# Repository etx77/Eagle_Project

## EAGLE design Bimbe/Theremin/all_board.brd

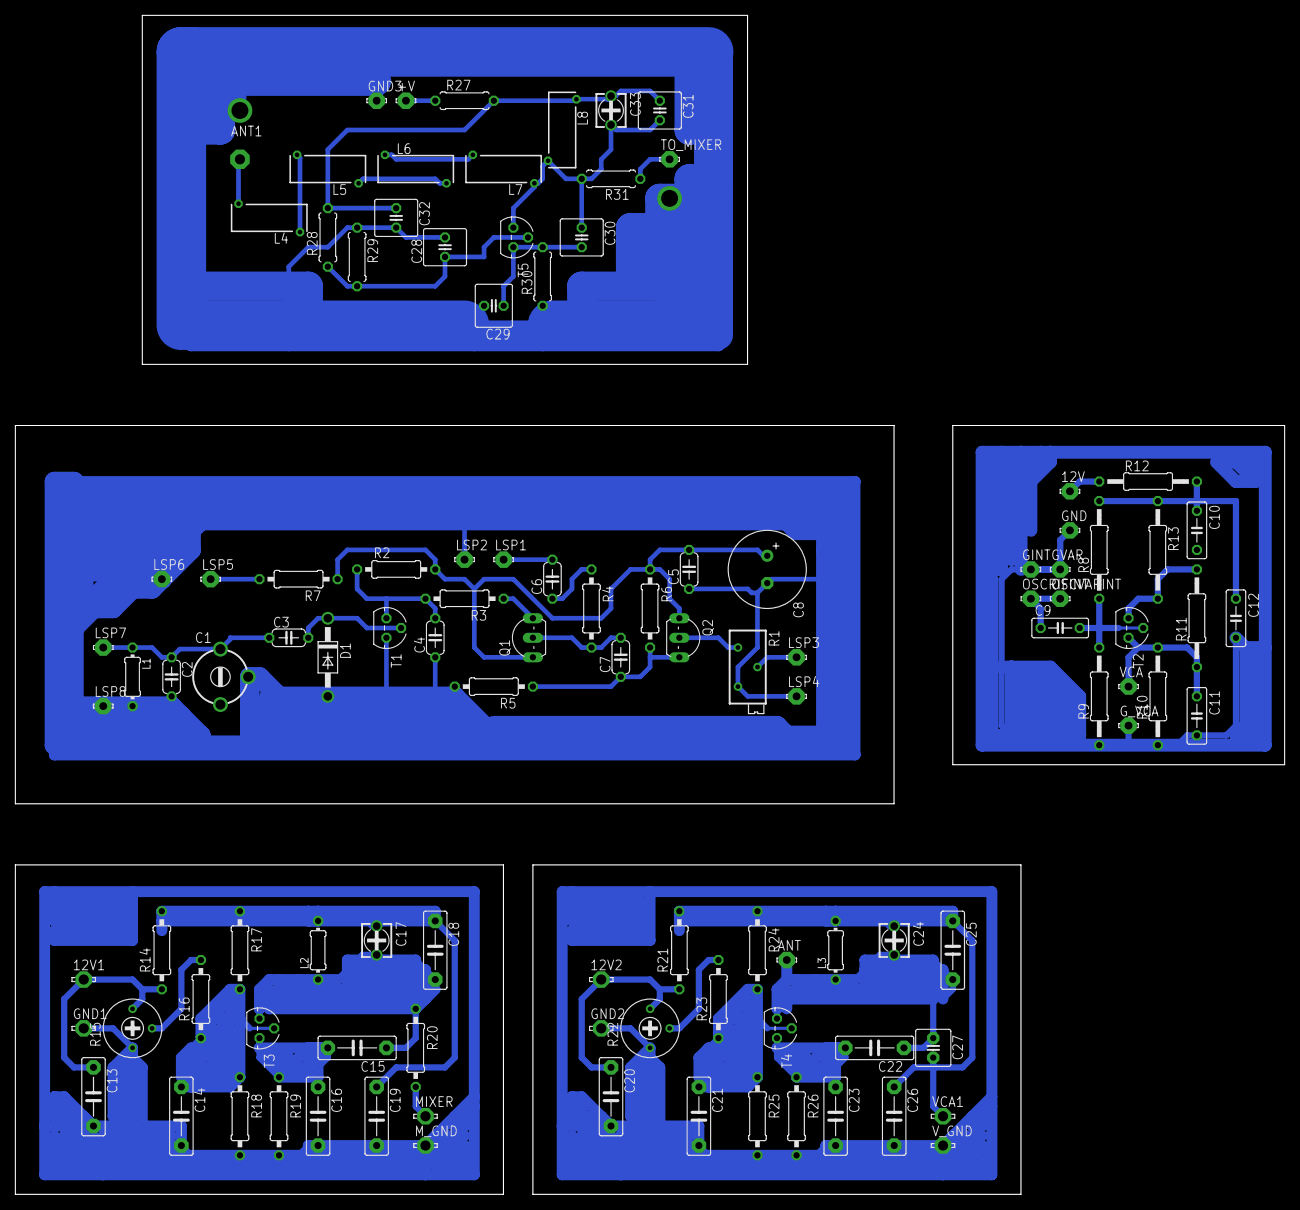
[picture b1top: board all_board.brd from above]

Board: 2 copper layers, 165.1 x 153.3 mm, 109 parts (0 on the bottom side), 47 nets.

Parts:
12V: LSP10
12V1, 12V2: LSP13
+V: LSP10
ANT: LSP10
ANT1: PAD-01
C1: 10/40pF; CTRIM808-BC
C2: 220pF; C050-024X044
C3, C6: 4,7pF; C050-024X044
C4, C5: 100nF; C050-024X044
C7: 1nF; C050-024X044
C8: 10uF; E3,5-10
C9: 10nF; C050-025X075
C10, C11: 4,7nF; C050-025X075
C12: 100nF; C050-025X075
C13, C14, C20, C21: 100nF; C7.5B3
C15: 680pF; C7.5B3
C16, C19, C26: 33nF; C7.5B3
C17, C24: 10/40 pF; 3008
C18, C25: 220pF; C7.5B3
C22: 270pF; C7.5B3
C23: 12nF; C7.5B3
C27: 4,7pF; C2.5-5
C28: 100nF; C025-060X050
C29, C32: 33nF; C025-060X050
C30: 680pF; C025-060X050
C31: 220pF; C025-060X050
C33: 10/40pF; 3008
D1: 1N4004; DO41-10
GINT: LSP10
GND, GND3: LSP10
GND1, GND2: LSP13
GVAR: LSP10
G_VCA: LSP10
L1, L3: 330uH; 0204/7
L2: 1mH; 0204/7
L4, L5, L6, L7: 10mH; Z28/7
L8: 1mH; Z28/7
LSP1, LSP2, LSP3, LSP4, LSP5, LSP6, LSP7, LSP8: LSP10
MIXER: LSP13
M_GND: LSP13
OSCRIFINT: LSP10
OSCVARINT: LSP10
Q1, Q2: 2N5486; TO92-
R1: 10K log; RTRIMT93XB
R2: 10K; 0207/10
R3: 470K; 0207/10
R4, R23: 1M; 0207/10
R5, R6: 4,7M; 0207/10
R7, R14, R19, R21, R26: 1K; 0207/10
R8: 560K; 0207/12
R9: 100k; 0207/12
R10, R11, R12: 1K; 0207/12
R13: 6K8; 0207/12
R15, R22: 10K Lin; RTRIM3339P
R16, R20: 330K; 0207/10
R17, R24: 150K; 0207/10
R18, R25: 33K; 0207/10
R27, R30: 1K; 0207/7
R28: 150K; 0207/7
R29: 33K; 0207/7
R31: 330K; 0207/7
T1, T2, T3, T4, T5: BC547; TO92
TO_MIXER: LSP10
VCA: LSP10
VCA1: LSP13
V_GND: LSP13

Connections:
unnamed: C1.1, C2.1, C3.1, L1.1, LSP7.MP
unnamed: C6.2, LSP1.MP
unnamed: C3.2, D1.C, T1.2
unnamed: C4.2, R2.1, R3.2, T1.3
unnamed: C5.2, C8.+, Q1.3, Q2.3, R2.2, R6.1, R7.1
unnamed: Q1.1, R3.1
unnamed: C6.1, R4.1
unnamed: C7.2, Q1.2, R4.2
unnamed: C7.1, Q2.1, R5.1, R6.2
unnamed: Q2.2, R1.1
unnamed: LSP3.MP, R1.2
unnamed: LSP5.MP, R7.2
unnamed: C9.2, R8.1, R9.2, T2.2
unnamed: C10.2, R11.2, R13.2, T2.3
unnamed: C11.1, R10.2, R11.1, T2.1, VCA.MP
unnamed: C1.2, C2.2, C4.1, C5.1, C8.-, D1.A, L1.2, LSP2.MP, LSP4.MP, LSP6.MP, LSP8.MP, R1.3, R5.2, T1.1
unnamed: C10.1, C12.1, R8.2, R12.2, R13.1
unnamed: C9.1, OSCRIFINT.MP, OSCVARINT.MP
unnamed: 12V.MP, R12.1
unnamed: C11.2, C12.2, GINT.MP, GND.MP, GVAR.MP, G_VCA.MP, R9.1, R10.1
unnamed: 12V1.MP, C13.1, R14.1, R15.3
unnamed: C17.+, C18.1, C19.1, L2.2, R14.2, R17.1
unnamed: C14.1, R16.1, R17.2, R18.1, T3.2
unnamed: R15.2, R16.2
unnamed: C15.2, C16.1, R19.1, T3.1
unnamed: MIXER.MP, R20.2
unnamed: C13.2, C14.2, C16.2, C19.2, GND1.MP, M_GND.MP, R15.1, R18.2, R19.2
unnamed: C15.1, C17.-, C18.2, L2.1, R20.1, T3.3
unnamed: 12V2.MP, C20.1, R21.1, R22.3
unnamed: C24.+, C25.1, C26.1, L3.2, R21.2, R24.1
unnamed: C21.1, R23.1, R24.2, R25.1, T4.2
unnamed: R22.2, R23.2
unnamed: C22.2, C23.1, R26.1, T4.1
unnamed: C27.2, VCA1.MP
unnamed: C20.2, C21.2, C23.2, C26.2, GND2.MP, R22.1, R25.2, R26.2, V_GND.MP
unnamed: ANT.MP, C22.1, C24.-, C25.2, C27.1, L3.1, T4.3
unnamed: C31.1, C32.1, C33.+, L8.2, R27.2, R28.2
unnamed: ANT1.1, L4.1
unnamed: L4.2, L5.1
unnamed: L5.2, L6.1
unnamed: L6.2, L7.1
unnamed: C30.1, C31.2, C33.-, L7.2, L8.1, R31.2, T5.3
unnamed: C28.1, R28.1, R29.2, T5.2
unnamed: C29.1, C30.2, R30.2, T5.1
unnamed: R31.1, TO_MIXER.MP
unnamed: +V.MP, R27.1
unnamed: C28.2, C29.2, C32.2, GND3.MP, R29.1, R30.1

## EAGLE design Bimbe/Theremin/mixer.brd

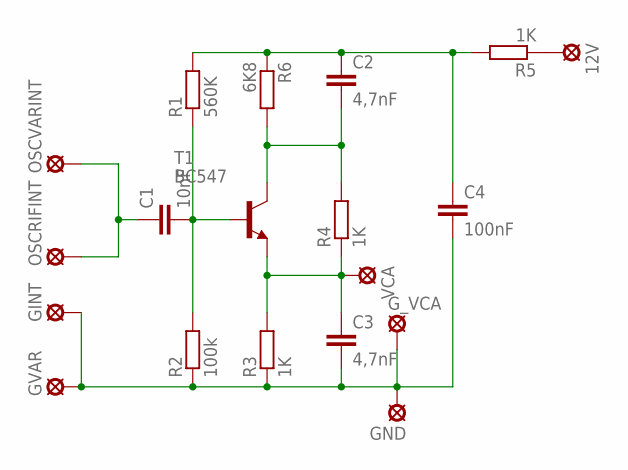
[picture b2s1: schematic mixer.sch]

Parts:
12V: LSP10
C1: 10nF; C050-025X075
C2, C3: 4,7nF; C050-025X075
C4: 100nF; C050-025X075
GINT: LSP10
GND: LSP10
GVAR: LSP10
G_VCA: LSP10
OSCRIFINT: LSP10
OSCVARINT: LSP10
R1: 560K; 0207/12
R2: 100k; 0207/12
R3, R4, R5: 1K; 0207/12
R6: 6K8; 0207/12
T1: BC547; TO92
VCA: LSP10

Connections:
unnamed: C1.2, R1.1, R2.2, T1.2 (B)
unnamed: C2.2, R4.2, R6.2, T1.3 (C)
unnamed: C3.1, R3.2, R4.1, T1.1 (E), VCA.MP
unnamed: C2.1, C4.1, R1.2, R5.2, R6.1
unnamed: C1.1, OSCRIFINT.MP, OSCVARINT.MP
unnamed: 12V.MP, R5.1
unnamed: C3.2, C4.2, GINT.MP, GND.MP, GVAR.MP, G_VCA.MP, R2.1, R3.1

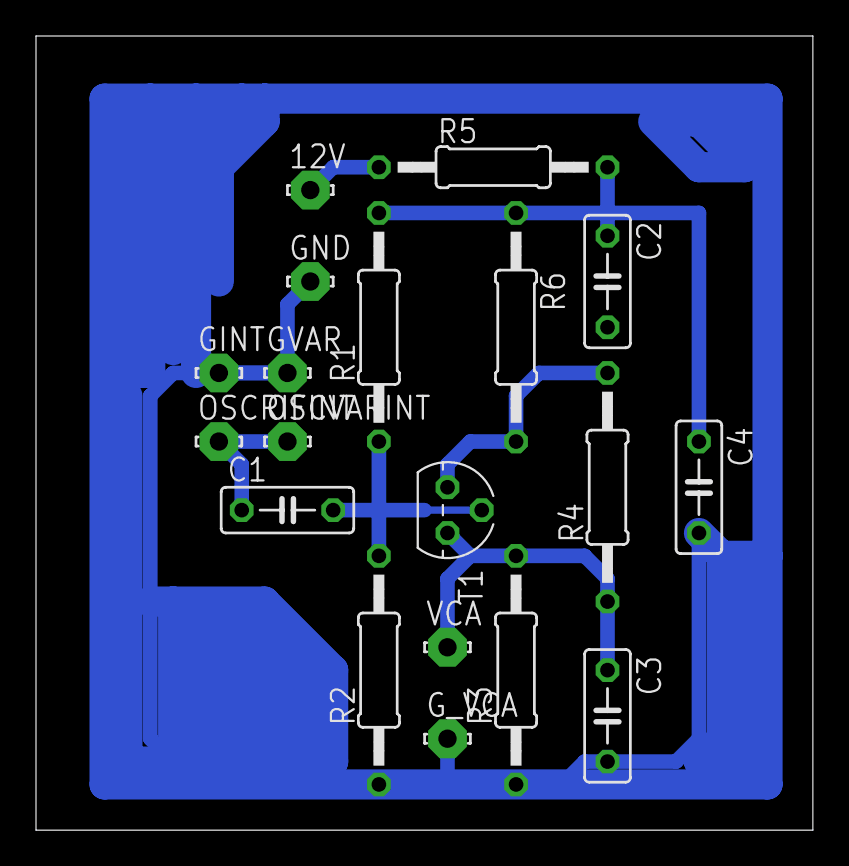
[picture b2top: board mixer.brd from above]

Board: 2 copper layers, 43.2 x 44.1 mm, 19 parts (0 on the bottom side), 7 nets.

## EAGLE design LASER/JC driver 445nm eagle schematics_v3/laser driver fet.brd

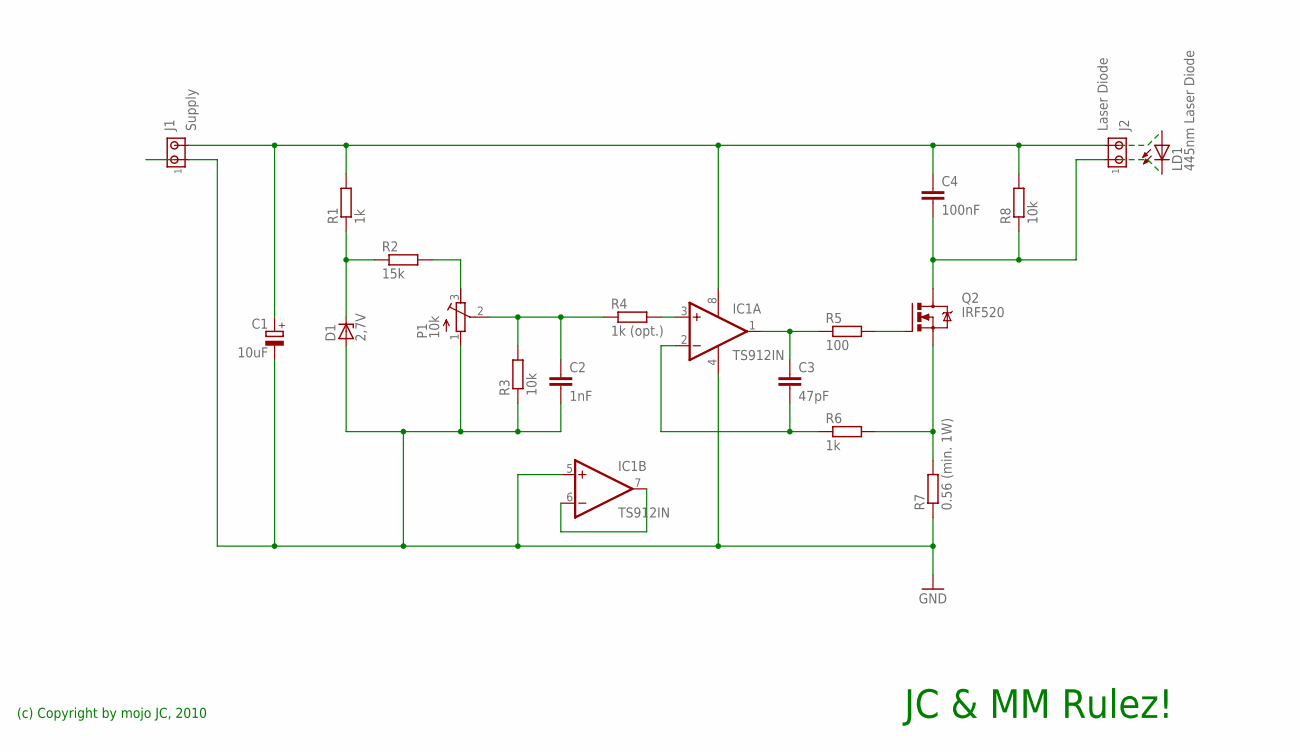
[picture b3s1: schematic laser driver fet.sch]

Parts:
C1: 10uF; E5-13
C2: 1nF; C2.5-3
C3: 47pF; C2.5-3
C4: 100nF; C2.5-3
D1: 2,7V; DO41Z10
IC1: TS912IN; DIL08
J1: Supply; 1X2MTA
J2: Laser Diode; 1X2MTA
LD1: 445nm Laser Diode; LED5MM
P1: 10k; RTRIM3296W
Q2: IRF520; TO220BV
R1, R6: 1k; 0309/10
R2: 15k; 0309/10
R3, R8: 10k; 0309/10
R4: 1k (opt.); 0309/10
R5: 100; 0309/10
R7: 0.56 (min. 1W); 0411V

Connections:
GND: C1.-, C2.2, D1.A, IC1.4 (V-), IC1.5 (+IN), J1.1, P1.1 (E), R3.1, R7.1
unnamed: D1.C, R1.1, R2.1
unnamed: C1.+, C4.1, IC1.8 (V+), J1.2, J2.2, R1.2, R8.2
unnamed: C4.2, J2.1, Q2.D, R8.1
unnamed: P1.3 (A), R2.2
unnamed: IC1.3 (+IN), R4.2
unnamed: C3.2, IC1.2 (-IN), R6.1
unnamed: Q2.S, R6.2, R7.2
unnamed: Q2.G, R5.2
unnamed: C3.1, IC1.1 (OUT), R5.1
unnamed: C2.1, P1.2 (S), R3.2, R4.1
unnamed: IC1.6 (-IN), IC1.7 (OUT)

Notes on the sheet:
(c) Copyright by mojo JC, 2010
JC & MM Rulez!

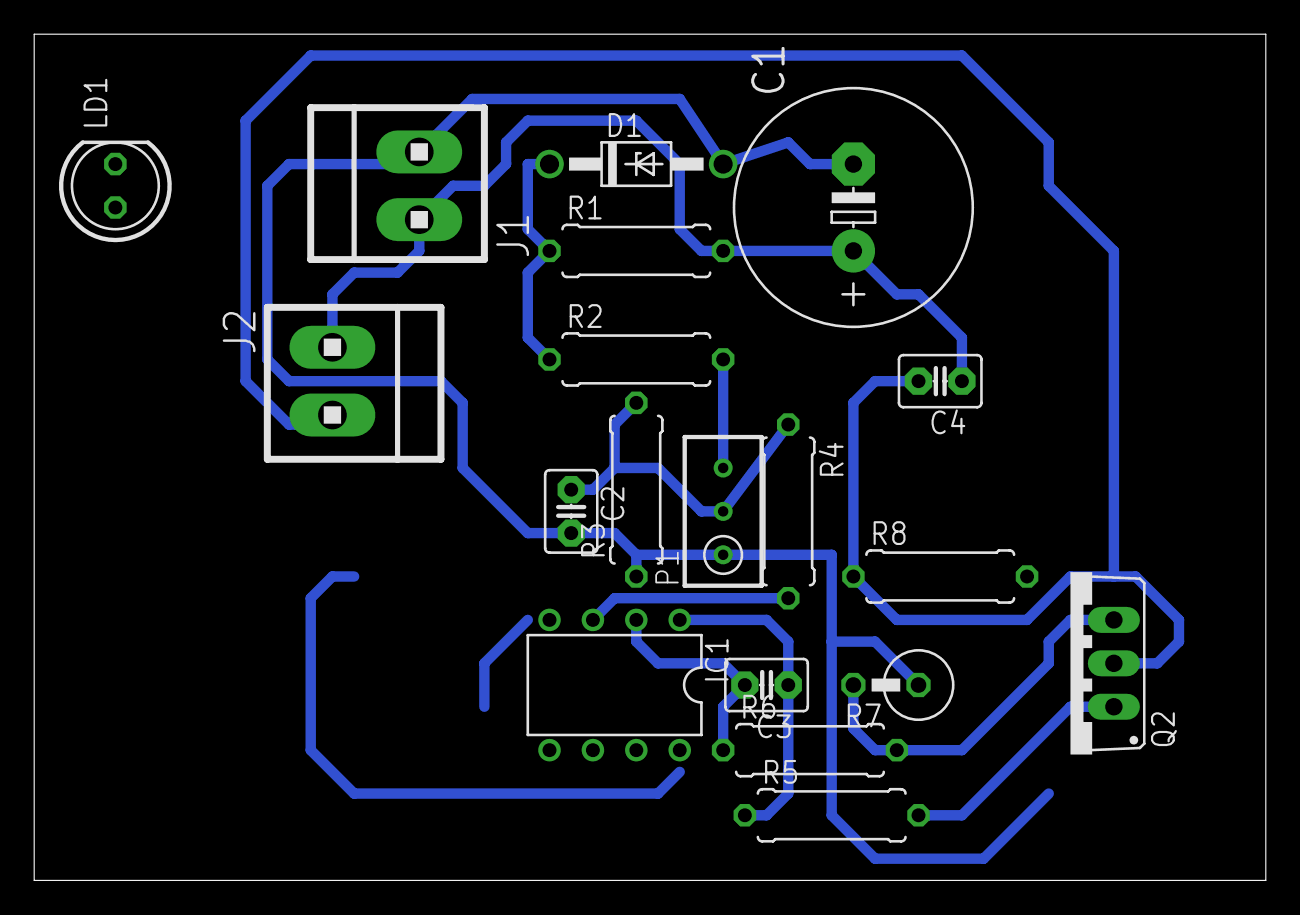
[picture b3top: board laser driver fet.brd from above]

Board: 2 copper layers, 72.1 x 49.5 mm, 19 parts (0 on the bottom side), 12 nets.

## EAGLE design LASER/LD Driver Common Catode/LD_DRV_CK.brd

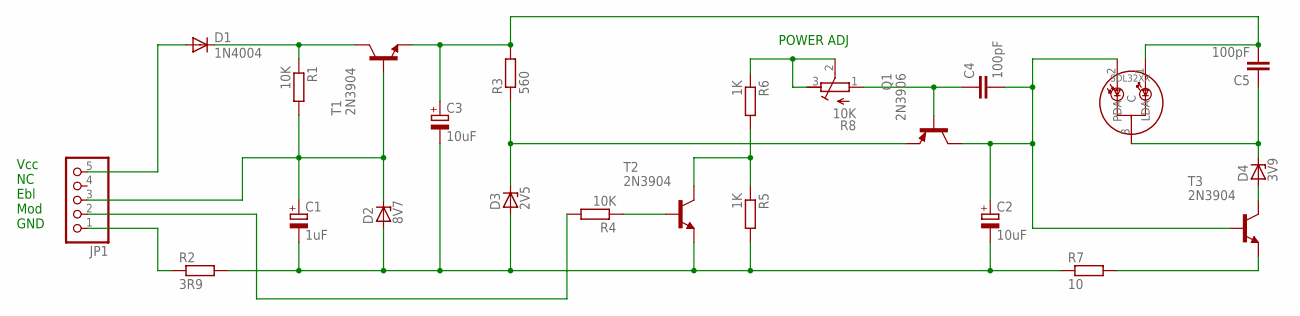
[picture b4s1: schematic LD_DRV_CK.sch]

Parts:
C1: 1uF; E2,5-6E
C2, C3: 10uF; E2,5-6E
C4, C5: 100pF; C025-030X050
D1: 1N4004; DO41-10
D2: 8V7; ZDIO-10
D3: 2V5; ZDIO-10
D4: 3V9; ZDIO-10
JP1: PINHD-1X5/90; 1X05/90
Q1: 2N3906; TO92
R1, R4: 10K; 0207/10
R2: 3R9; 0207/10
R3: 560; 0207/10
R5, R6: 1K; 0207/10
R7: 10; 0207/10
R8: 10K; RTRIM3339P
SLD32XX_1: SLD32XX; SLD32XXVF
T1, T2, T3: 2N3904; TO92

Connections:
unnamed: D1.C, R1.1, T1.1 (C)
unnamed: C1.+, D2.C, JP1.3, R1.2, T1.2 (B)
unnamed: C1.-, C2.-, C3.-, D2.A, D3.A, R2.2, R5.2, R7.1, T2.3 (E)
unnamed: D3.C, Q1.3 (E), R3.1
unnamed: R4.1, T2.2 (B)
unnamed: C3.+, C5.2, R3.2, SLD32XX_1.1 (LDA), T1.3 (E)
unnamed: JP1.2, R4.2
unnamed: JP1.1, R2.1
unnamed: D1.A, JP1.5
unnamed: R5.1, R6.2, T2.1 (C)
unnamed: R6.1, R8.2 (S), R8.3 (E)
unnamed: C4.1, Q1.2 (B), R8.1 (A)
unnamed: C2.+, C4.2, Q1.1 (C), SLD32XX_1.2 (PDA), T3.2 (B)
unnamed: R7.2, T3.3 (E)
unnamed: C5.1, D4.C, SLD32XX_1.3 (C)
unnamed: D4.A, T3.1 (C)

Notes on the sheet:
Vcc NC Ebl Mod GND
POWER ADJ

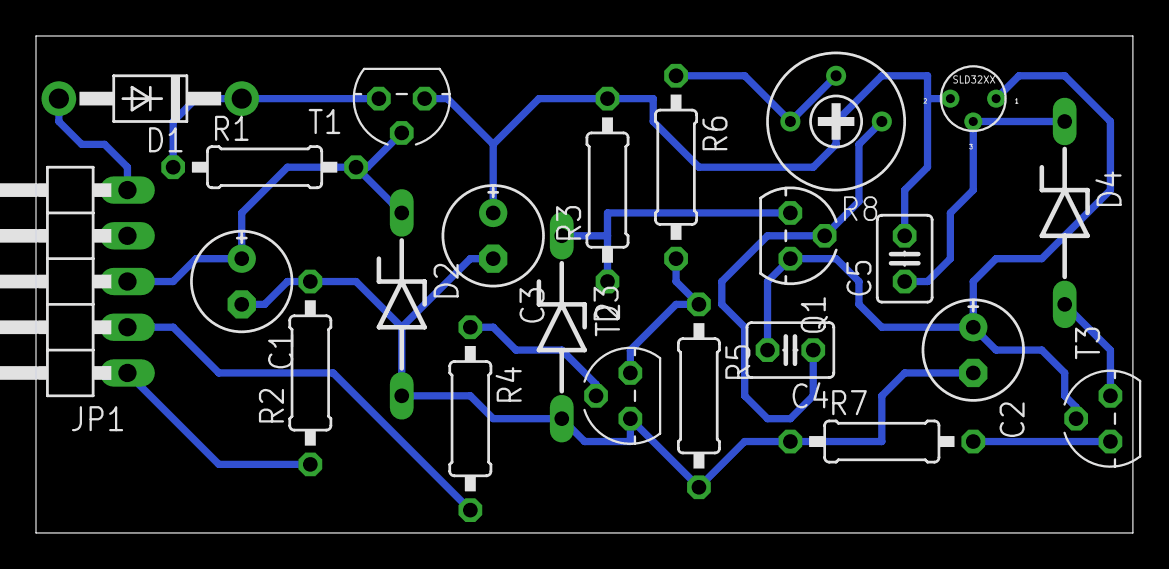
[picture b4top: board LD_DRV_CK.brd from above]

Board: 2 copper layers, 60.9 x 27.6 mm, 23 parts (0 on the bottom side), 16 nets.

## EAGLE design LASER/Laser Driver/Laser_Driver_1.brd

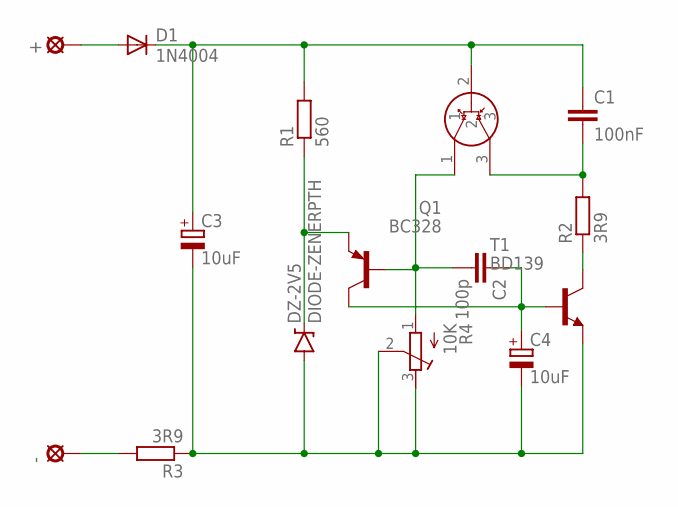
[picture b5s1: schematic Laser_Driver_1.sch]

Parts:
+: LSP10
-: LSP10
C1: 100nF; C5B5
C2: 100p; C5B5
C3, C4: 10uF; E2,5-6E
D1: 1N4004; DO41-10
DZ-2V5: DIODE-ZENERPTH; DIODE-ZENER
LDIR_1: LD_IR; LASER_IR_TO18
Q1: BC328; TO92-EBC
R1: 560; 0207/7
R2, R3: 3R9; 0207/7
R4: 10K; RTRIM3339P
T1: BD139; TO126

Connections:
unnamed: +.MP, D1.A
unnamed: -.MP, R3.2
unnamed: C1.1, C3.+, D1.C, LDIR_1.2, R1.2
unnamed: C3.-, C4.-, DZ-2V5.P$2 (A), R3.1, R4.2 (S), R4.3 (E), T1.1 (E)
unnamed: C2.2, LDIR_1.1, Q1.B, R4.1 (A)
unnamed: C1.2, LDIR_1.3, R2.2
unnamed: C2.1, C4.+, Q1.C, T1.3 (B)
unnamed: R2.1, T1.2 (C)
unnamed: DZ-2V5.P$1 (C), Q1.E, R1.1

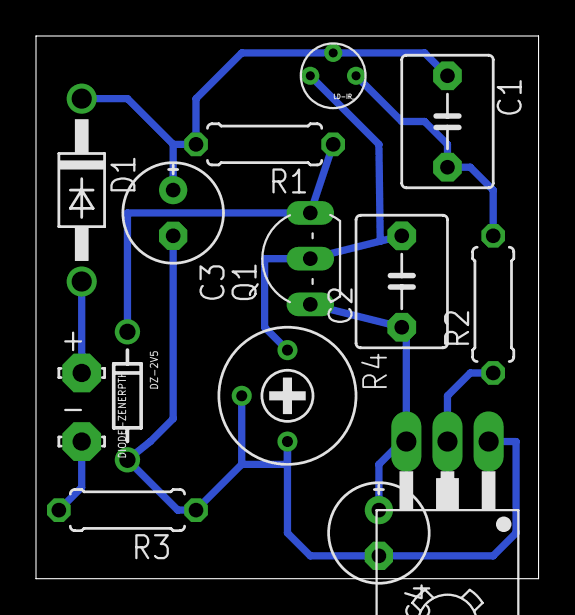
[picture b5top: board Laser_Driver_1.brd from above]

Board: 2 copper layers, 27.9 x 30.1 mm, 15 parts (0 on the bottom side), 9 nets.

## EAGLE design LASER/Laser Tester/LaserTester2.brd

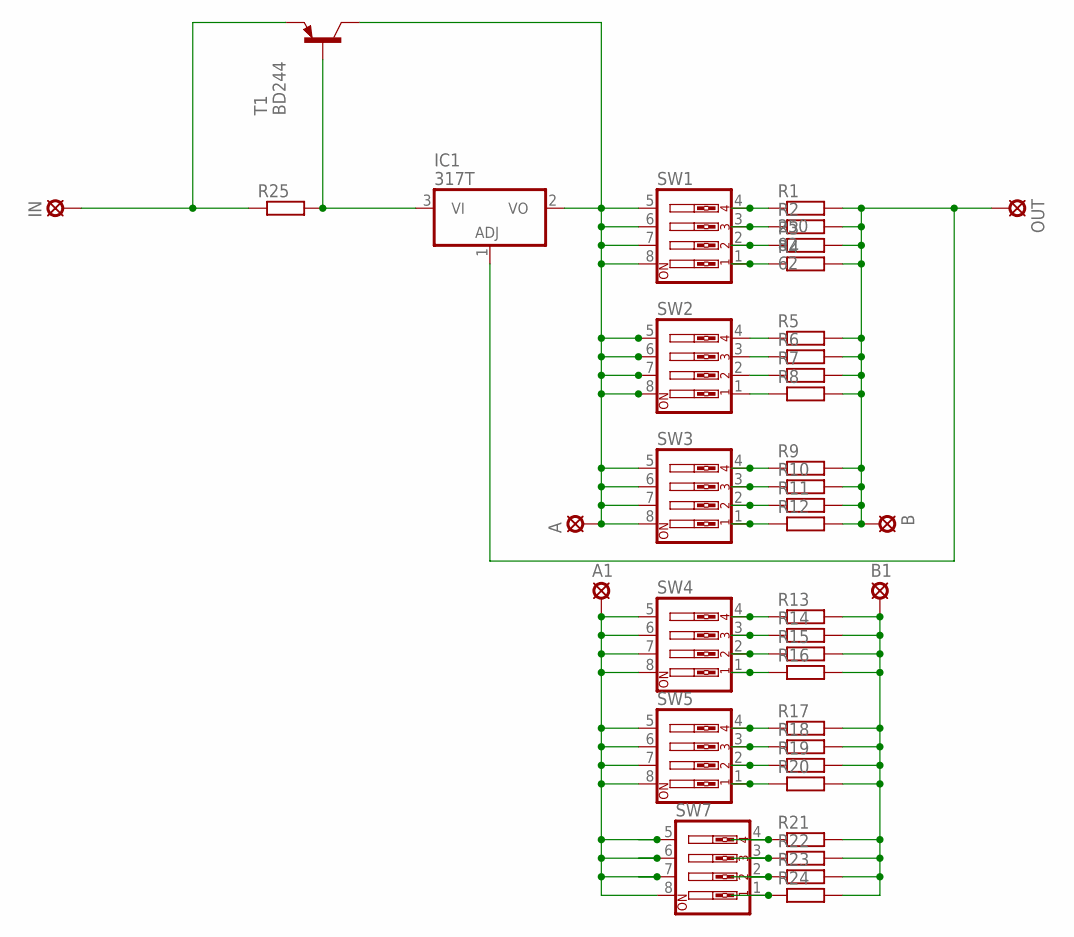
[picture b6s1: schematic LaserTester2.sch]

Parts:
A, A1: LSP10
B, B1: LSP10
IC1: 317T; TO220H
IN: LSP10
OUT: LSP10
R1: 250; 0207/10
R2: 82; 0207/10
R3: 62; 0207/10
R4, R5, R6, R7, R8, R9, R10, R11, R12, R13, R14, R15, R16, R17, R18, R19, R20, R21, R22, R23, R24, R25: R-EU_0207/10; 0207/10
SW1, SW2, SW3, SW4, SW5, SW7: SW_DIP-4; EDG-04
T1: BD244; TO220

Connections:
unnamed: A.MP, IC1.2 (VO), SW1.5, SW1.6, SW1.7, SW1.8, SW2.5, SW2.6, SW2.7, SW2.8, SW3.5, SW3.6, SW3.7, SW3.8, T1.2 (C)
unnamed: A1.MP, SW4.5, SW4.6, SW4.7, SW4.8, SW5.5, SW5.6, SW5.7, SW5.8, SW7.5, SW7.6, SW7.7, SW7.8
unnamed: B1.MP, R13.2, R14.2, R15.2, R16.2, R17.2, R18.2, R19.2, R20.2, R21.2, R22.2, R23.2, R24.2
unnamed: R13.1, SW4.4
unnamed: R14.1, SW4.3
unnamed: R15.1, SW4.2
unnamed: R16.1, SW4.1
unnamed: R17.1, SW5.4
unnamed: R18.1, SW5.3
unnamed: R19.1, SW5.2
unnamed: R20.1, SW5.1
unnamed: R21.1, SW7.4
unnamed: R22.1, SW7.3
unnamed: R23.1, SW7.2
unnamed: R24.1, SW7.1
unnamed: R5.1, SW2.4
unnamed: R6.1, SW2.3
unnamed: R7.1, SW2.2
unnamed: R8.1, SW2.1
unnamed: R9.1, SW3.4
unnamed: R10.1, SW3.3
unnamed: R11.1, SW3.2
unnamed: R12.1, SW3.1
unnamed: R1.1, SW1.4
unnamed: R2.1, SW1.3
unnamed: R3.1, SW1.2
unnamed: R4.1, SW1.1
unnamed: IC1.3 (VI), R25.2, T1.1 (B)
unnamed: IN.MP, R25.1, T1.3 (E)
unnamed: B.MP, IC1.1 (ADJ), OUT.MP, R1.2, R2.2, R3.2, R4.2, R5.2, R6.2, R7.2, R8.2, R9.2, R10.2, R11.2, R12.2

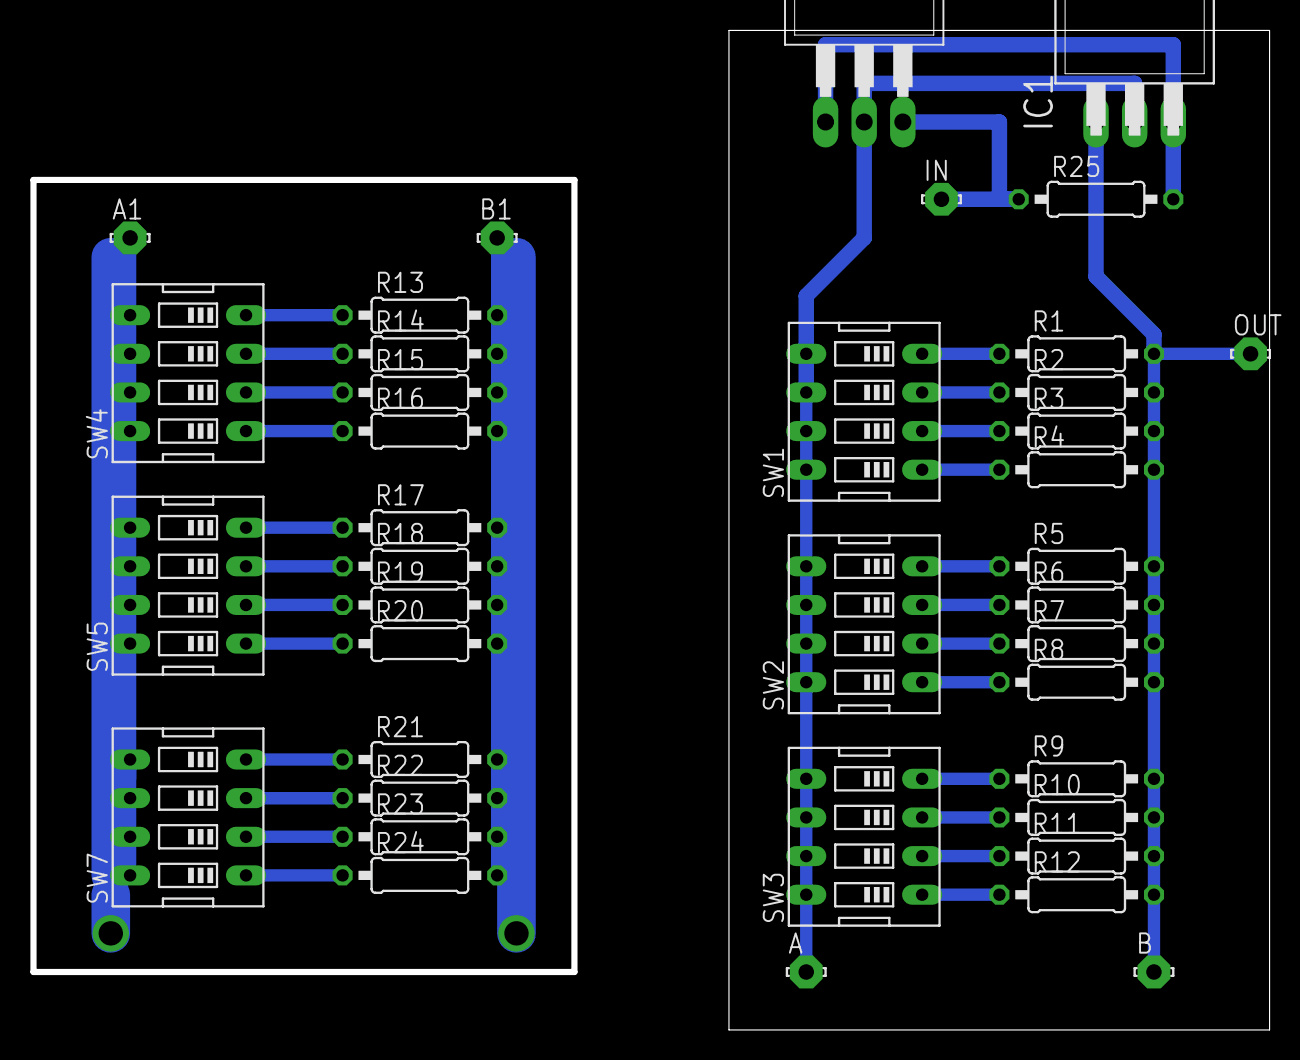
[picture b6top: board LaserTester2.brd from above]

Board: 2 copper layers, 81.3 x 65.7 mm, 39 parts (0 on the bottom side), 30 nets.

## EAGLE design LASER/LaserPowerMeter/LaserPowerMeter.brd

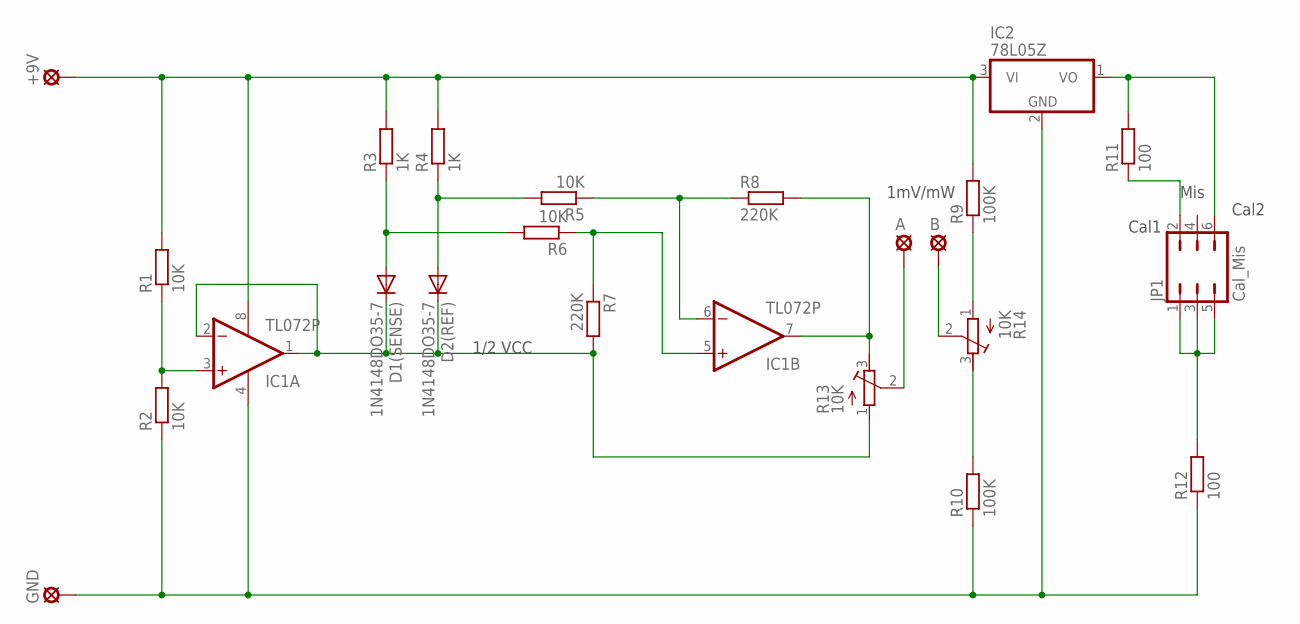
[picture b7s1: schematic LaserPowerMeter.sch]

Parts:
+9V: LSP10
A: LSP10
B: LSP10
D1(SENSE), D2(REF): 1N4148DO35-7; DO35-7
GND: LSP10
IC1: TL072P; DIL08
IC2: 78L05Z; TO92
JP1: Cal_Mis; JP3Q
R1, R2, R5, R6: 10K; 0204/7
R3, R4: 1K; 0204/7
R7, R8: 220K; 0204/7
R9, R10: 100K; 0204/7
R11, R12: 100; 0204/7
R13, R14: 10K; RTRIM3339P

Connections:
unnamed: JP1.1, JP1.3, JP1.5, R12.2
unnamed: GND.MP, IC1.4 (V-), IC2.2 (GND), R2.1, R10.1, R12.1
unnamed: IC1.3 (+IN), R1.1, R2.2
unnamed: IC2.1 (VO), JP1.6, R11.2
unnamed: JP1.2, R11.1
unnamed: +9V.MP, IC1.8 (V+), IC2.3 (VI), R1.2, R3.2, R4.2, R9.2
unnamed: R9.1, R14.1 (A)
unnamed: R10.2, R14.3 (E)
unnamed: A.MP, R13.2 (S)
unnamed: B.MP, R14.2 (S)
unnamed: IC1.7 (OUT), R8.2, R13.3 (E)
unnamed: D1(SENSE).A, R3.1, R6.2
unnamed: D2(REF).A, R4.1, R5.2
unnamed: IC1.6 (-IN), R5.1, R8.1
unnamed: IC1.5 (+IN), R6.1, R7.1
unnamed: D1(SENSE).C, D2(REF).C, IC1.1 (OUT), IC1.2 (-IN), R7.2, R13.1 (A)

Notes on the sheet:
1mV/mW
1/2 VCC
Cal1
Cal2
Mis

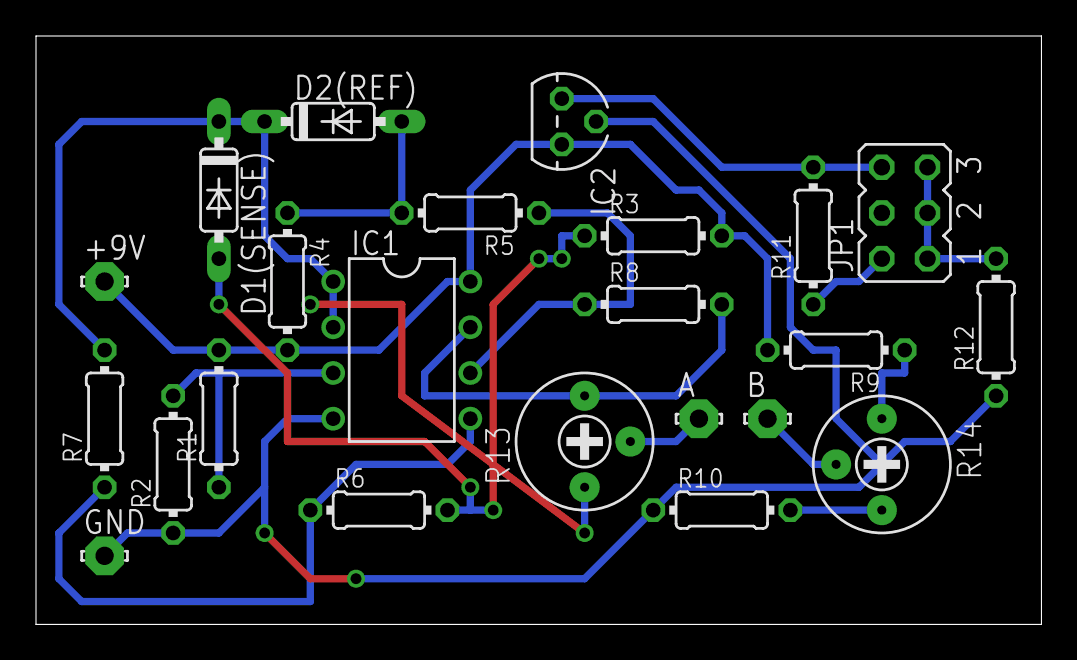
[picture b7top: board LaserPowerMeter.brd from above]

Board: 2 copper layers, 55.9 x 32.7 mm, 23 parts (0 on the bottom side), 16 nets.

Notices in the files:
parts and their libraries:
SparkFun-DiscreteSemi: Licensing: Creative Commons ShareAlike 4.0 International - https://creativecommons.org/licenses/by-sa/4.0
